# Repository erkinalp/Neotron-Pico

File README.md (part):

# Neotron Pico BTX

> A Neotron system powered by the Raspberry Pi Pico, in a micro-BTX form-factor.

NOTE: This is a work in progress. Proper micro-BTX layout will be uploaded in some time

The Neotron Pico BTX is based around the idea of the [Neotron-32](https://github.com/neotron-compute/Neotron-32-Hardware), but using a low-cost Raspberry Pi Pico instead of a Texas Instuments Tiva-C Launchpad. It also stretches out to full micro-BTX size, and adds more expansion slots so that you can easily design and add your own peripherals.

## Design

The Raspberry Pi Pico is the core of the Neotron Pico. It uses PIO statemachines to generate 12-bit Super VGA video, and digital 16 bit 48 kHz stereo audio. It also has both I²C and SPI buses. SPI chipselects and IRQs are handled by an SPI-to-GPIO expander. This provides eight chip-selects and eight IRQs, to support up to eight expansion slots or peripherals. The eight chip-selects can be globally disabled, allowing the Pico to talk to either the I/O exander, or the selected expansion slot. The board has an SD Card fitted in the 'Slot 1' position, and the Board Management Controller in the 'Slot 0' position, leaving 'Slot 2' through to 'Slot 7' available for expansion. Each expansion slot has both I²C and SPI, along with unique chip-select and IRQ signals.

## Software

The Neotron Pico BTX is designed to run the Neotron OS - a CP/M or MS-DOS alike OS written in Rust. But, being open-hardware, you can program your Neotron Pico to do pretty much anything.

## Specs

* Dual Cortex-M0+
  * One dedicated for video/audio
  * One available for OS/Application use
* 264 KiB SRAM
* 2 MiB Boot ROM
* Micro-ATX form-factor
* SD Card slot for storage
* 12V DC input
* SPI and I²C based expansion bus
  * Four externally accessible expansion slots
  * Debug headers with signals for two more slots
* Dual PS/2 ports for Keyboard + Mouse
* 16-bit 48 kHz stereo audio headphone out, line out, line in, and microphone in
* 12-bit (4096 colour) VGA video output
  * Capable of 40x25, 80x25 and 80x50 text modes
  * Capable of 640x480 @ 60 Hz 16-colour, 320x240 @ 60 Hz / 300x200 @ 70 Hz 256-colour graphics modes
* Designed to run the Neotron OS
* Open Source Hardware
* Perfectly suitable for passive cooling
* Low power
* Designed for hand assembly

## Components in detail

### Processor

The main processor module is the Raspberry Pi Pico, which features:

* A Raspberry Pi Silicon RP2040 SoC
  * Dual-core Cortex-M0+ @ 133 MHz
  * 264 KiB internal SRAM
  * No internal Flash
  * USB 1.1
  * SPI, UART, I²C and _Programmable I/O_ peripherals
* 26 GPIO pins
* 2 MiB QSPI Flash
* On-board LED
* On-board 5V to 3.3V regulator
* USB 2.0 Full-speed OTG micro-AB port
* 4.00 USD / 3.60 GBP retail price

The limited I/O on the Pico (we are using half the available pins just for the video output) is supplemented using a Microchip MCP23S17 SPI to GPIO expander, and an octal buffer. See the [I/O Expanders](#io-expanders) section for more details.

| Pin  | Name | Signal        | Function                                           |
| :--- | :--- | :------------ | :------------------------------------------------- |
| 01   | GP0  | VGA_HSYNC     | VGA Horizontal Sync (31.5 kHz)                     |
| 02   | GP1  | VGA_VSYNC     | VGA Vertical Sync (60 Hz/70 Hz)                    |
| 04   | GP2  | VGA_RED0      | Digital VGA signal, Red channel LSB                |
| 05   | GP3  | VGA_RED1      | Digital VGA signal, Red channel                    |
| 06   | GP4  | VGA_RED2      | Digital VGA signal, Red channel                    |
| 07   | GP5  | VGA_RED3      | Digital VGA signal, Red channel MSB                |
| 09   | GP6  | VGA_GREEN0    | Digital VGA signal, Green channel LSB              |
| 10   | GP7  | VGA_GREEN1    | Digital VGA signal, Green channel                  |
| 11   | GP8  | VGA_GREEN2    | Digital VGA signal, Green channel                  |
| 12   | GP9  | VGA_GREEN3    | Digital VGA signal, Green channel MSB              |
| 14   | GP10 | VGA_BLUE0     | Digital VGA signal, Blue channel LSB               |
| 15   | GP11 | VGA_BLUE1     | Digital VGA signal, Blue channel                   |
| 16   | GP12 | VGA_BLUE2     | Digital VGA signal, Blue channel                   |
| 17   | GP13 | VGA_BLUE3     | Digital VGA signal, Blue channel MSB               |
| 19   | GP14 | I2C_SDA       | I²C Data                                           |
| 20   | GP15 | I2C_SCL       | I²C Clock                                          |
| 21   | GP16 | SPI_CIPO      | SPI Data In                                        |
| 22   | GP17 | nSPI_CS_IO    | Low selects MCP23S17, High selects Peripherals     |
| 24   | GP18 | SPI_CLK       | SPI Clock                                          |
| 25   | GP19 | SPI_COPI      | SPI Data Out                                       |
| 26   | GP20 | nIRQ_IO       | Interrupt Request Input from MCP23S17              |
| 27   | GP21 | nOUTPUT_EN    | Enable buffered CS outputs from MCP23S17           |
| 29   | GP22 | I2S_ADC_DATA  | Digital Audio Input                                |
| 31   | GP26 | I2S_DAC_DATA  | Digital Audio Output                               |
| 32   | GP27 | I2S_BIT_CLOCK | Digital Audio Bit Clock (1.536MHz)                 |
| 34   | GP28 | I2S_LR_CLOCK  | Digital Audio Sync (96kHz)                         |

### Super VGA output

The Raspberry Pi Silicon RP2040 generates 12-bit VGA video at a range of standard resolutions (including 640x480 @ 60 Hz).

* 15-pin D-Sub VGA interface
* 12-bit (4-4-4) RGB R2R DAC
* 3peak TPF133A or Texas Instruments THS7316 RGB video buffer
   * 36 MHz bandwidth - 1024x768@60Hz maximum
   * 6dB gain
   * Drives 75 ohm standard VGA interface
   * SOIC-8 package (1.27mm pitch)
* Texas Instruments TPD7S019 Sync/DDC level shifter and RGB EMC filter
   * SSOP-16 package (0.635mm pitch)

The design could easily be adapted to remove the TPF133A/THS7316 video buffer and the TPD7S019 level shifter/filter, and instead use the [1BitSquared DVI PMOD](https://1bitsquared.com/collections/fpga/products/pmod-digital-video-interface) board if you prefer a DVI output (using an HDMI connector).

### Audio Codec

The audio subsystem offers 16-bit 48 kHz stereo audio in and out through a classic blue/green/pink triple 3.5mm TRS jack. Input and Output volume can be software controlled.

* Texas Instruments TLV320AIC23B
  * I²S + I²C interface
  * Amplified 32mW headphone output and line out
  * Microphone in and line in
  * TSSOP-28 package (0.635mm pitch)
* Triple 3.5mm TRS jack (Kycon STX-4335-5BGP-S1)
  * Headphone Out (green)
  * Line In (blue)
  * Microphone In (pink)
* AC'97 Pin Header for ATX cases with Audio Jacks
  * Headphone Out
  * Microphone In
* Extra line-level output pin header (e.g. for additional RCA audio jacks - operates in addition to 3.5mm headphone jack output)
* Internal line-level input pin header (e.g. for CD-ROM audio - disabled when 3.5mm line-in jack in-use)

### Board Management Controller

Power-on Reset sequencing, soft shutdown, voltage monitoring and PS/2 interfacing is handled by a separate STM32F0 SoC.

* ST Micro STM32F0 (STM32F030K6T6) microcontroller
  * 32-bit Arm Cortex-M0+ Core
  * 3.3V I/O (5V tolerant)
  * 32 KiB Flash
  * 4 KiB SRAM
  * LQFP-32 package (0.8mm pitch)
* Controls two PS/2 ports
* Monitors 5V and 3.3V rails
* Controls system reset, soft-on and soft-off for main CPU
   * Can turn the main 5V regulator on and off
   * Runs from 3.3V stand-by regulator
* SPI interface (with dedicated IRQ line) with main CPU
* Secondary I²C bus, connected to VGA DDC pins

| Pin  | Name | Signal      | Function                                  |
| :--- | :--- | :---------- | :---------------------------------------- |
| 02   | PF0  | BUTTON_nPWR | Power Button Input (active low)           |
| 03   | PF1  | BUTTON_nRST | Reset Button Input (active low)           |
| 06   | PA0  | MON_3V3     | 3.3V rail monitor Input (1.65V nominal)   |
| 07   | PA1  | MON_5V      | 5.0V rail monitor Input (1.65V nominal)   |
| 08   | PA2  | SYS_nRESET  | System Reset Output (active low)          |
| 09   | PA3  | DC_ON       | Enable 5.0V PSU Output (active high)      |
| 10   | PA4  | SPI1_nCS    | SPI Chip Select Input (active low)        |
| 11   | PA5  | SPI1_SCK    | SPI Clock Input                           |
| 12   | PA6  | SPI1_CIPO   | SPI Data Output                           |
| 13   | PA7  | SPI1_COPI   | SPI Data Input                            |
| 14   | PB0  | LED0        | PWM output for first Status LED           |
| 15   | PB1  | LED1        | PWM output for second Status LED          |
| 18   | PA8  | IRQ_nHOST   | Interrupt Output to the Host (active low) |
| 19   | PA9  | I2C1_SCL    | I²C Clock                                 |
| 20   | PA10 | I2C1_SDA    | I²C Data                                  |
| 21   | PA11 | USART1_CTS  | UART Clear-to-Send Output                 |
| 22   | PA12 | USART1_RTS  | UART Ready-to-Receive Input               |
| 23   | PA13 | SWDIO       | SWD Progamming Data Input                 |
| 24   | PA14 | SWCLK       | SWD Programming Clock Input               |
| 25   | PA15 | PS2_CLK0    | Keyboard Clock Input                      |
| 26   | PB3  | PS2_CLK1    | Mouse Clock Input                         |
| 27   | PB4  | PS2_DAT0    | Keyboard Data Input                       |
| 28   | PB5  | PS2_DAT1    | Mouse Data Input                          |
| 29   | PB6  | USART1_TX   | UART Transmit Output                      |
| 30   | PB7  | USART1_RX   | UART Receive Input                        |

Note that in the above table, the UART signals are wired as _Data Terminal Equipment (DTE)_.

This design should also be pin-compatible with the following SoCs (although the software may need recompiling):

* STM32F042K4Tx
* STM32F042K6Tx
* STM32L071KBTx
* STM32L071KZTx
* STM32L072KZTx
* STM32L081KZTx
* STM32L082KZTx

Note that not all STM32 pins are 5V-tolerant, and the PS/2 protocol is a 5V open-collector system, so ensure that whichever part you pick has 5V-tolerant pins (marked `FT` or `FTt` in the datasheet) for the PS/2 signals. All of the parts above _should_ be OK, but they haven't been tested. Let us know if you try one!

### PS/2 Keyboard and Mouse

* Kycon two-port stacked 6-pin DIN sockets (Kycon KMDGX-6S/6S-S4N)
* Controlled via Board Management Controller

### Power Supply

* 12V nominal input
  * 8V to 30V is OK if you don't need the 12V rail
  * Fused with a PTC at 2A
  * Reverse polarity protected
* 3A 5.0V main regulator (DC-DC switch-mode regulator module)
  * Morsun K7805-3AR3
* 200mA 3.3V stand-by regulator (a micropower linear regulator running from 12V input)
* 1A 3.3V regulator (a high-power 1117 type linear regulator running from 5.0V rail)
* Controlled and monitored by the Board Management Controller

### Real Time Clock

The Neotron Pico can retain time/date settings when fully powered off, using a Real Time Clock chip and a CR2032 lithium coin cell. This also retains system settings in a very low-power SRAM built into the Real Time Clock chip.

* MCP7940N or DS1307Z+ Real Time Clock
* CR2032 battery-backup (should be OK for about 10 years)
* 56 bytes of battery-backed SRAM for system settings

### I/O Expander

* MCP23S17 SPI to GPIO expander (DIP)
* 74HC138 3:8 decoder (SOIC-16)
* Five debug LEDs
* Eight Chip-Select outputs (active low)
* Eight IRQ inputs (active high or active low)

Because we used so many pins on the Pico for Audio and Video, we don't have enough pins to use for _Chip Select_ lines. Each device we wish to communicate with on the SPI bus must have a unique chip select line and so have limited lines means we could only have a limited number of SPI devices.

However, in this design, we cheat and use a Microchip MCP23S17 I/O expander. This is an SPI peripheral with 16 GPIO pins that can be controlled by sending it commands over SPI. It also has an IRQ output which be programmed to fire when the input pins match a certain state. The MCP23S18 (with open-drain outputs) will *not* work - it has a different pinout.

The problem would come when the Pico has finished talking to our select SPI device - how does it tell the MCP23S17 to release the current chip select, without the SPI bus traffic also going to the currently selected expansion slot? We resolve this by using a simple 8-bit decoder/buffer with an enable pin. This allows the Pico to disconnect all of the chip select signals at once, regardless of the output of the MCP23S17. Once this is disabled, we know we are talking to only the MCP23S17 and the Pico can command it to select the next chip select of interest to us.

Interrupts are also processed through the MCP23S17. We configure the device to provide an IRQ (edge, active low) whenever any of the eight IRQ inputs are active (programmable for edge or level, active high/rising or low/falling). When the Pico receives an IRQ from the MCP23S17, it must do a read of the pins (using SPI) to find out which device actually raised the interrupt. This model is similar to that used in the IBM PC - where the Intel 8088 must talk to an Intel 8259A programmable interrupt controller over the ISA bus to find out which interrupt was raised - except that in our case, our CPU is very fast and our bus is pretty slow, so our interrupt latency isn't very good. Worse, if there is a big SPI transaction happening (such as transferring a 512 byte block from an SD card) when an interrupt fires, the Pico will have to wait for that to complete before it can talk to the MCP23S17 to handle the IRQ. That or it could just drop the SPI transaction mid-way through and re-try it later (if your expansion device can tolerate such rudeness).

```
+------+                                  +-----+
|      |----------/OUTPUT_EN------------->|     |
|      |                                  |     |
|      |           +----------+           |     |
|      |           |          |           |     |
|      |           |          |--CS_SEL0->|     |----/CS0---------------------------------+
|      |           |          |           |     |                                         |
|      |           |          |--CS_SEL1->|  D  |----/CS1-----------------------------+   |
|      |           |          |           |  E  |                                     |   |
|      |           |          |--CS_SEL2->|  C  |----/CS2-------------------------+   |   |
|      |           |          |           |  O  |                                 |   |   |
|      |           |          |           |  D  |----/CS3---------------------+   |   |   |
|      |           |          |           |  E  |                             |   |   |   |
|      |           |          |           |  R  |----/CS4-----------------+   |   |   |   |
|      |           |          |           |     |                         |   |   |   |   |
|      |           |          |           |     |----/CS5-------------+   |   |   |   |   |
|      |           |          |           |     |                     |   |   |   |   |   |
|      |           |          |           |     |----/CS6---------+   |   |   |   |   |   |
| Pico |           | MCP23S17 |           |     |                 |   |   |   |   |   |   |
|      |           |          |           |     |----/CS7-----+   |   |   |   |   |   |   |
|      |           |          |           +-----+             v   v   v   v   v   v   v   v
|      |           |          |                             +---+---+---+---+---+---+---+---+
|      |--/IOCS--->|          |                             | S | S | S | S | S | S | S | S |
|      |<---IRQ----|          |                             | l | l | l | l | l | l | l | l |
|      |<===SPI===>|          |<============SPI============>| o | o | o | o | o | o | o | o |
|      |           |          |                             | t | t | t | t | t | t | t | t |
|      |           |          |                             |   |   |   |   |   |   |   |   |
|      |           |          |                             | 7 | 6 | 5 | 4 | 3 | 2 | 1 | 0 |
|      |           |          |                             +---+---+---+---+---+---+---+---+
|      |           |          |<---IRQ7-----------------------+   |   |   |   |   |   |   |
|      |           |          |                                   |   |   |   |   |   |   |
|      |           |          |<---IRQ6---------------------------+   |   |   |   |   |   |
|      |           |          |                                       |   |   |   |   |   |
|      |           |          |<---IRQ5-------------------------------+   |   |   |   |   |
|      |           |          |                                           |   |   |   |   |
|      |           |          |<---IRQ4-----------------------------------+   |   |   |   |
|      |           |          |                                               |   |   |   |
|      |           |          |<---IRQ3---------------------------------------+   |   |   |
|      |           |          |                                                   |   |   |
|      |           |          |<---IRQ2-------------------------------------------+   |   |
|      |           |          |                                                       |   |
|      |           |          |<---IRQ1-----------------------------------------------+   |
|      |           |          |                                                           |
|      |           |          |<---IRQ0---------------------------------------------------+
+------+           +----------+
```

## Expansion

The seven expansion sockets allow you to add on I²C or SPI based devices at a later date. Each provides a single chip-select and a single IRQ line - the motherboard design should ensure each socket gets a unique signal for each of these. Each expansion device should also contain a AT24C256 or similar EEPROM device. To allow these EEPROM devices to be scanned, each slot also contains three `EEPROM_ADDRESS` pins, tied to Vcc or GND in a unique combination. These should be connected through to the EEPROM address lines on your AT24C256, thus ensuring that each expansion card has its EEPROM at a unique address - 0x50 on Slot 0 through to a maximum possible 0x57 for Slot 7. Where your board has on-board devices, you should fit an AT24C256 EEPROM for each device so that the on-board devices can be discovered, exactly as if they were on an expansion card.

The expansion slot is a simple 2x10 header. We suggest the use of a TE card-edge connector, but you could equally use two 1x10 pin-headers if desired.

The expansion connector pinout is:

```
               +--------+
     SPI_COPI -| 1    2 |- GND
     SPI_CIPO -| 3    4 |- GND
      SPI_CLK -| 5    6 |- GND
      ~SPI_CS -| 7    8 |- ~IRQ
      I2C_SDA -| 9   10 |- I2C_SCL
 EEPROM_ADDR0 -| 11  12 |- EEPROM_ADDR1
 EEPROM_ADDR2 -| 13  14 |- ~RESET
           5V -| 15  16 |- 5V
          3V3 -| 17  18 |- 3V3
          GND -| 19  20 |- GND
               +--------+
```

Four expansion slots line up with the ATX case expansion brackets, allowing you to use cards with external connectors. Note that these are aligned the "PCI way around" with components facing away from the board's I/O area, rather than the "ISA way around" which would have the components facing the I/O area. A further three of the expansion slots are available for internal use only.

### Slot Assignments

#### Slot 0

The signals for *Slot 0* are connected to the Board Management Controller. Both CS and IRQ are connected.

#### Slot 1

The signals for *Slot 1* are connected to the on-board SD Card Slot. CS 1 is connected to the card's `DAT3` pin, and IRQ 1 is connected to the `Card Detect` pin on the card slot.

#### Slot 2

*Slot 2* is the right-most Expansion Slot.

#### Slot 3

*Slot 3* is the right-most-but-one Expansion Slot.

#### Slot 4

*Slot 4* is the left-most-but-one Expansion Slot.

#### Slot 5

*Slot 5* is the left-most Expansion Slot.

#### Slot 6

*Slot 6* is not fitted. SPI Chip Select 6 and IRQ 6 are only available on the test headers. 

#### Slot 7

*Slot 7* is not fitted. SPI Chip Select 7 and IRQ 7 are only available on the test headers. 

### Main I²C Bus

All I²C device address given below are 7-bit values. Note that with I²C, the first byte in a message is the _control byte_; this is comprised of the device address in the top seven bits, and an extra bit at the bottom to indicate read (1) or write (0).

The memory addresses given are 8-bit values used to access the contents of an I²C device, and are usually supplied as the second byte in a message.

* Device Address 0x1A - TLV320AIC23
  * Memory Address 0x00 - Left line input channel volume control
  * Memory Address 0x01 - Right line input channel volume control
  * Memory Address 0x02 - Left channel headphone volume control
  * Memory Address 0x03 - Right channel headphone volume control
  * Memory Address 0x04 - Analog audio path control
  * Memory Address 0x05 - Digital audio path control
  * Memory Address 0x06 - Power down control
  * Memory Address 0x07 - Digital audio interface format
  * Memory Address 0x08 - Sample rate control
  * Memory Address 0x09 - Digital interface activation
  * Memory Address 0x0F - Reset register
* Device Address 0x52 - Slot 2 ID EEPROM
  * Memory Addresses 0x00..0xFF - Expansion Card Specification in NEID (Neotron Expansion ID) format
* Device Address 0x53 - Slot 3 ID EEPROM
  * Memory Addresses as per Slot 1
* Device Address 0x54 - Slot 4 ID EEPROM
  * Memory Addresses as per Slot 1
* Device Address 0x55 - Slot 5 ID EEPROM
  * Memory Addresses as per Slot 1
* Device Address 0x68 - Real-time Clock (DS1307+ variant)
  * Memory Addresses 0x00..0x07 - Clock Configuration
  * Memory Addresses 0x08..0x3F - Battery-backed SRAM
* Device Address 0x6F - Real-time Clock (MCP7940N variant)
  * Memory Addresses 0x00..0x1F - Clock Configuration
  * Memory Addresses 0x20..0x5F - Battery-backed SRAM

### Secondary I²C Bus

There is a second I²C bus, driven by the Board Management Controller. This is connected to the Display Data Connection (DDC) pins on the VGA interface, allowing the reading of the VGA monitor's [EDID block](https://en.wikipedia.org/wiki/Extended_Display_Identification_Data). This is typically at device address `0x50`

## Expansion Ideas

Why not design and build your own expansion card? You could try designing:

* A dual Atari/SEGA 9-pin Joypad Interface
* A Mikro Electronika Click adaptor, allow many of the range of [Click boards](https://www.mikroe.com/click) to be fitted
* A Wi-Fi/Bluetooth card, using an Espressif ESP32-C3
* A second processor card - perhaps with a RISC-V microcontroller, or classic Zilog Z80
* An OPL2 or OPL3 based FM synthesiser card
* An ISA adaptor card (taking an ISA card at right-angles, i.e. parallel to the base board) - a simple microcontroller should be able to bit-bang the ISA bus at 8 MHz and offer an SPI peripheral interface to the Neotron Expansion Slot
* An IDE interface card, allowing 40-pin IDE Hard Disk Drives and CD-ROM drives to be used - this will be quite similar to an ISA bus adaptor
* A floppy drive controller card - either using an eSPI Super I/O chip, or connecting a legacy ISA bus floppy controller as per the ISA adaptor
* A video card for a second monitor output, perhaps based on the CPLD used in the [VGAtonic](https://hackaday.io/project/6309-vga-graphics-over-spi-and-serial-vgatonic)

## Automated Builds

This project treats a PCB like embedded firmware:

* The *source files* are the KiCAD 6 files (in `./Kicad`)
* The *compiler* is KiCAD 6, plus various automation plug-ins (like KiBom)
* The *build system* is [KiBot](https://github.com/INTI-CMNB/KiBot)
* The *build outputs* are PDF versions of the schematic and the PCB, plus various zipped Gerber and Drill files.

We do not check *build outputs* into this repository - *ever*. Instead, we run a Github Action which uses KiBot to generate our outputs. On a regular Pull Request, the *build outputs* are stored as *artefacts* against the particular Github Action run. When a new version is tagged, the *build outputs* are stored as files against a [Github Release](https://github.com/Neotron-Compute/Neotron-Pico/releases).

You can build locally using the KiBot docker container:

```console
~/Neotron-Pico $ docker run --rm -ti -v $(pwd):/work setsoft/kicad_auto:dev_k6
root@12345678:/# cd /work/Kicad
root@12345678:/work/Kicad# kibot -c docs.kibot.yml -e neotron-pico.kicad_sch -b neotron-pico.kicad_pcb -d docs
```

This will build everything and put it in the `./Kicad/docs` directory.

## Changelog

See [CHANGELOG.md](./CHANGELOG.md) for a list of detailed changes.

## Licence

These documents, schematics and PCB designs are Copyright (c) The Neotron Developers, 2022.

This work is licensed under a [Creative Commons Attribution-ShareAlike 4.0 International License](http://creativecommons.org/licenses/by-sa/4.0/).

That means you are free to:

* share - copy and redistribute the material in any medium or format
* adapt — remix, transform, and build upon the material for any purpose, even commercially

Please note that the models provided in the [Kicad/Models](./Kicad/Models) directory are from various manufacturers. Terms and conditions for the use of the models are as specified by the original manufacturer/author.

__NOTE__: Releases are provided free-of-charge, and without any kind of warranty - explicit or implied. It is imperative you validate the design for yourself before placing an order or using/adapting/copying any of the designs herein. The Neotron Developers cannot be held responsible if you build or remix our designs and it doesn't turn out how you expected. This is a work-in-progress and you will most likely need to fix something, somewhere.

## Contribution Agreement

Unless you explicitly state otherwise, any contribution intentionally submitted for inclusion in the work by you, as defined in the Apache-2.0 license, shall be licensed as above, without any additional terms or conditions.

## Articles and Reviews

* [Tom's Hardware](https://www.tomshardware.com/uk/news/raspberry-pi-pico-neotron-motherboard)
* [Tom's Hardware #2](https://www.tomshardware.com/uk/news/raspberry-pi-pico-motherboard-update-neotron-pico)
* [Hackaday](https://hackaday.com/2021/06/22/pi-pico-powered-atx-motherboard/)
* [Hackster.io](https://www.hackster.io/news/jonathan-pallant-s-neotron-pico-turns-the-raspberry-pi-pico-into-a-full-size-atx-pc-motherboard-fff86e2a1a96)
* [Hacker News](https://news.ycombinator.com/item?id=27627631)
* [Adafruit Blog](https://blog.adafruit.com/2021/06/23/a-raspberry-pi-pico-based-computer-motherboard/)

## Datasheets and References

* Raspberry Pi Pico
  * Datasheet: <https://datasheets.raspberrypi.org/pico/pico-datasheet.pdf>
* Raspberry Pi Silicon RP2040
  * Datasheet: <https://datasheets.raspberrypi.org/rp2040/rp2040-datasheet.pdf>
  * Hardware Design Guide: <https://datasheets.raspberrypi.org/rp2040/hardware-design-with-rp2040.pdf>
* ST Microelectronics STM32F031K6T6
  * Datasheet: <https://www.st.com/resource/en/datasheet/stm32f031k6.pdf>
* Morsun K7805-3AR3
  * Datasheet: <https://www.mornsunpower.de/html/pdf/K7805-3AR3.html>
* Texas Instruments TLV320AIC23BPW
  * Datasheet: <https://www.ti.com/lit/ds/symlink/tlv320aic23b.pdf>
  * Note TLV320AIC23B**I**PW is Industrial Temperature Range (and is fine to use), and TLV320AIC23BPW**R** is on a Reel (also fine)
* Texas Instruments THS7316
  * Datasheet: <https://www.ti.com/lit/ds/symlink/ths7316.pdf>
* Texas Instruments TPD7S019
  * Datasheet: <https://www.ti.com/lit/ds/symlink/tpd7s019.pdf>
* Microchip 24LC256 EEPROM
  * Info Page: <https://www.microchip.com/wwwproducts/en/24LC256>
* Microchip MCP7940N Real-Time Clock
  * Info Page: <https://www.microchip.com/wwwproducts/en/MCP7940N>

## How hard is this to solder?

Typically, I get the boards from JLCPCB with most of the surface-mount components already fitted. This includes all the LEDS, small inductors, resistors and small capacitors (all 0805 size), the transistors (all SOT-23), and whichever of the larger ICs they happen to have in stock. All that's left is the larger ICs, and the through-hole connectors.

In the release area, you will see a JLCPCB specific bill-of-materials (BoM), which includes only the parts with a `Cxxxx` format LCSC/JLCPCB part number. You upload this, along with the *CPL* position file for those parts, when placing your order.

If you want to order bare boards, it is designed to be hand-solderable. That's why there are no SMD parts smaller than 0805.

| Part           | Footprint | Size (mm) | Pitch (mm) |
|:---------------|:---------:|:---------:|:----------:|
| MCP23S17       |  DIP-28   |  36x7.6   |    2.54    |
| Jellybeans     |   0805    |  2.0x1.2  |    N/A     |
| Transistors    |  SOT-23   |  3.1x1.4  |    1.80    |
| 74HC138        |  SOIC-16  |  3.9x9.9  |    1.27    |
| THS7316        |  SOIC-8   |  3.9x4.9  |    1.27    |
| DS1307Z        |  SOIC-8   |  3.9x4.9  |    1.27    |
| STM32F031K6T6  |  LQFP-32  |  7.0x7.0  |    0.80    |
| TLV320AIC23BPW | TSSOP-28  |  4.4x9.7  |    0.65    |
| TPD7S019       |  SSOP-16  |  3.9x4.9  |   0.635    |

## But can I buy the parts yet?

Feel free to click these (unaffiliated) links and see for yourself!

| Component               | Manufacturer      | Part Number     | Octopart                                                                     | LCSC                                                                                                                | JLCPCB                                                                                | Digikey                                                                                                 | Mouser                                                                                                          | RS                                                                            | Farnell                                                                                                        |
| :---------------------- | :---------------- | :-------------- | :--------------------------------------------------------------------------- | :------------------------------------------------------------------------------------------------------------------ | :------------------------------------------------------------------------------------ | :------------------------------------------------------------------------------------------------------ | :-------------------------------------------------------------------------------------------------------------- | :---------------------------------------------------------------------------- | :------------------------------------------------------------------------------------------------------------- |
| Main CPU                | Raspberry Pi      | Pico (SC0915)   | [Link](https://octopart.com/raspberry+pi+pico-raspberry+pi-116179381?r=sp)   | N/A                                                                                                                 | N/A                                                                                   |                                                                                                         |                                                                                                                 | N/A                                                                           | [Link](https://uk.rs-online.com/web/p/raspberry-pi/2122162)                                                    |
| BMC                     | ST Micro          | STM32F030K6T6   | [Link](https://octopart.com/stm32f030k6t6-stmicroelectronics-30038872?r=sp)  | [C46830](https://www.lcsc.com/product-detail/ST-Microelectronics_STMicroelectronics-STM32F030K6T6_C46830.html)      | [C46830](https://jlcpcb.com/parts/componentSearch?isSearch=true&searchTxt=C46830)     | [Tray](https://www.digikey.co.uk/en/products/detail/stmicroelectronics/STM32F030K6T6/4494296)           | [Link](https://www.mouser.co.uk/ProductDetail/STMicroelectronics/STM32F030K6T6?qs=eyrSuY1LhL2nYlb0JDdrAA%3D%3D) | [Link](https://uk.rs-online.com/web/p/microcontrollers/8294644)               | [Link](https://uk.farnell.com/stmicroelectronics/stm32f030k6t6/mcu-32bit-cortex-m0-48mhz-lqfp/dp/2432085)      |
| BMC (alt)               | ST Micro          | STM32F031K6T6   | [Link](https://octopart.com/stm32f031k6t6-stmicroelectronics-35036651?r=sp)  | [C526904](https://www.lcsc.com/product-detail/ST-Microelectronics_STMicroelectronics-STM32F031K6T6_C526904.html)    | [C526904](https://jlcpcb.com/parts/componentSearch?isSearch=true&searchTxt=C526904)   | [Tray](https://www.digikey.co.uk/en/products/detail/stmicroelectronics/STM32F031K6T6/5051261)           | [Link](https://www.mouser.co.uk/ProductDetail/STMicroelectronics/STM32F031K6T6?qs=s5SkPsIz109XuZAtCLiKdA%3D%3D) | [Link](https://uk.rs-online.com/web/p/microcontrollers/1920937)               | [Link](https://uk.farnell.com/stmicroelectronics/stm32f031k6t6/mcu-32bit-48mhz-lqfp-32/dp/3129831)             |
| Video Amplifier         | Texas Instruments | THS7316         | [Link](https://octopart.com/ths7316dr-texas+instruments-7112464?r=sp)        | [C544774](https://www.lcsc.com/product-detail/Operational-Amplifier_Texas-Instruments-THS7316DR_C544774.html)       | [C544774](https://jlcpcb.com/parts/componentSearch?isSearch=true&searchTxt=C544774)   | [Tape](https://www.digikey.co.uk/en/products/detail/texas-instruments/THS7316DR/1905373)                | N/A                                                                                                             | N/A                                                                           | N/A                                                                                                            |
| Video Amplifier (alt 1) | 3Peak             | TPF133A         | [Link](https://octopart.com/tpf133a-sr-3peak-99349217?r=sp)                  | [C155446](https://www.lcsc.com/product-detail/Video-Amplifiers_3PEAK-TPF133A-SR_C155446.html)                       | [C155446](https://jlcpcb.com/parts/componentSearch?isSearch=true&searchTxt=C155446)   | N/A                                                                                                     | N/A                                                                                                             | N/A                                                                           | N/A                                                                                                            |
| Video Amplifier (alt 2) | DIOO              | DIO2663         | [Link](https://octopart.com/dio2663cs8-dioo-120986996?r=sp)                  | [C444605](https://lcsc.com/product-detail/Video-Amplifiers_DIOO-DIO2663CS8_C444605.html)                            | [C444605](https://jlcpcb.com/parts/componentSearch?isSearch=true&searchTxt=C444605)   | N/A                                                                                                     | N/A                                                                                                             | N/A                                                                           | N/A                                                                                                            |
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
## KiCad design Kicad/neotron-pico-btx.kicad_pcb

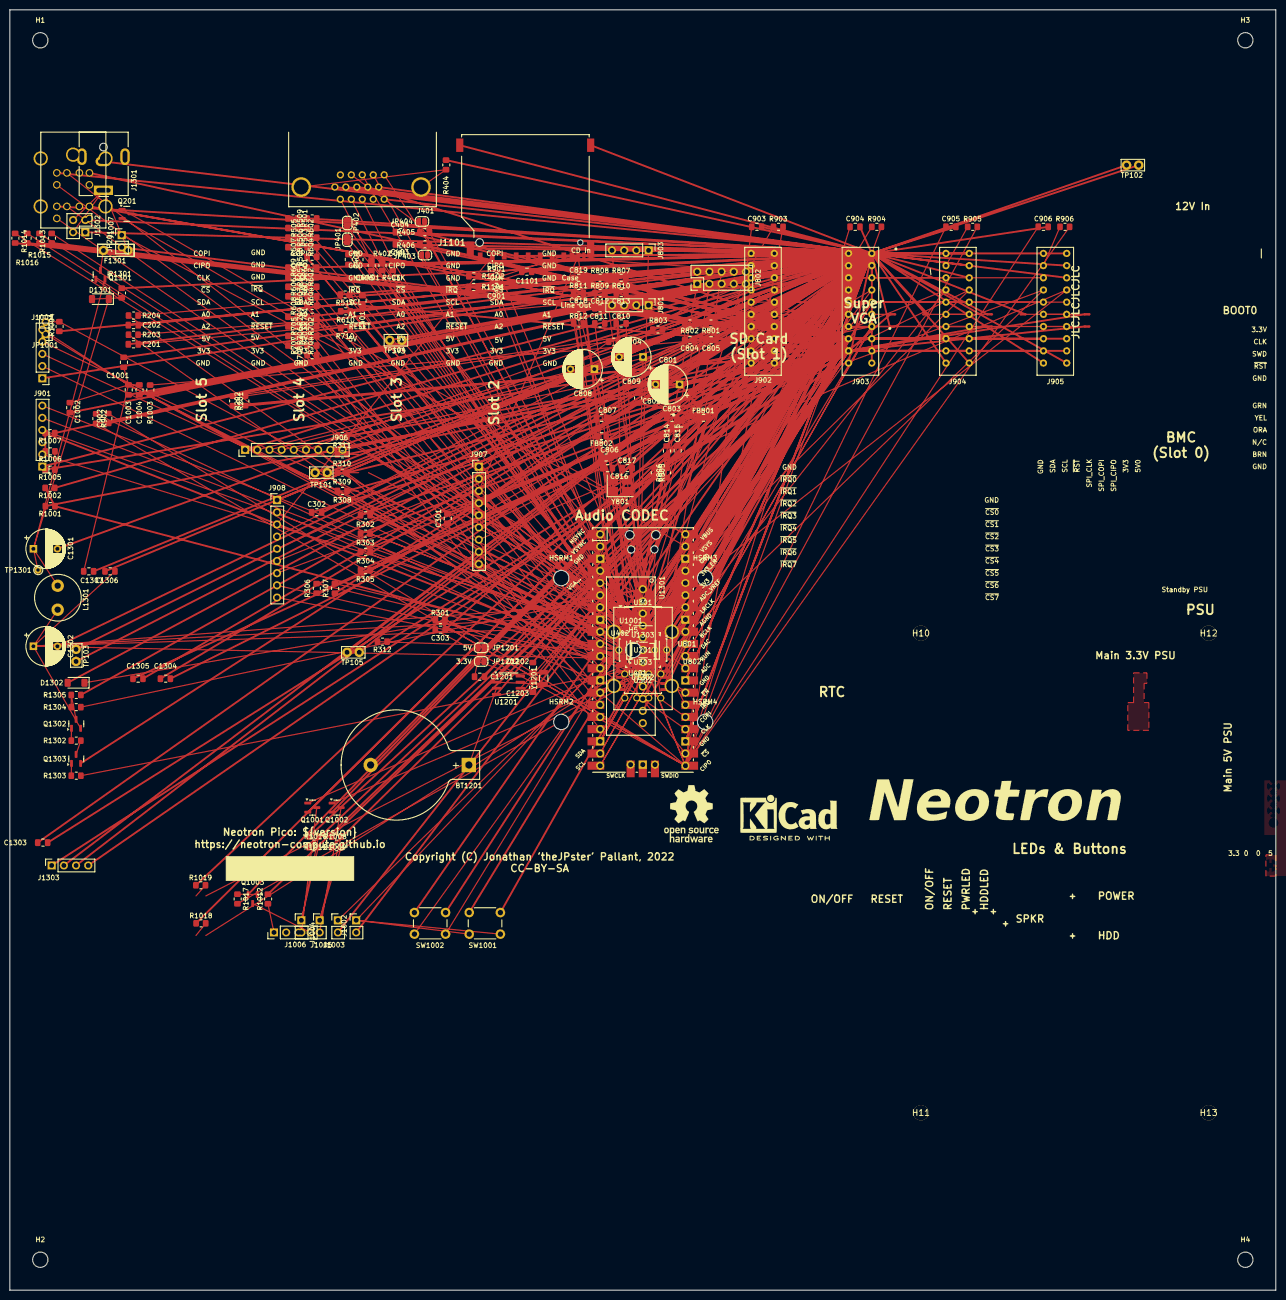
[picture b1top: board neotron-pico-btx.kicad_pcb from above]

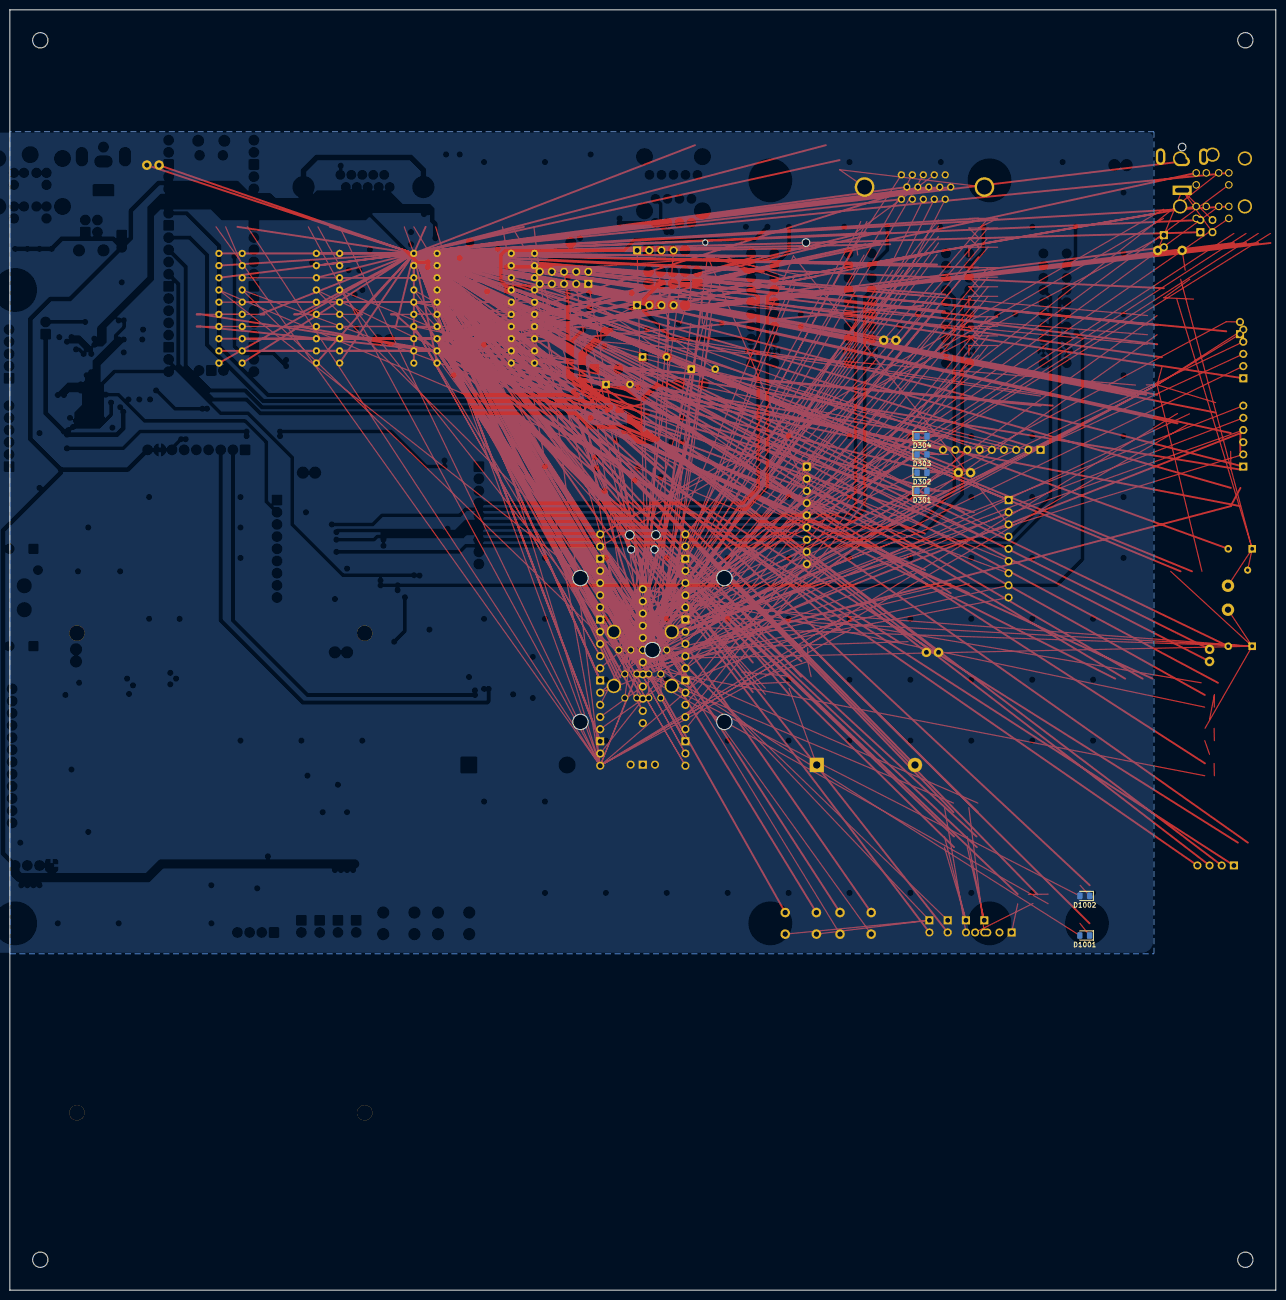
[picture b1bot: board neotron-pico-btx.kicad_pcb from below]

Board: 4 copper layers, 264.0 x 267.0 mm, 248 parts (6 on the bottom side), 190 nets.

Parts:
BT1201: CR2032; BatteryHolder_Keystone_103_1x20mm
C201, C202, C303, C901, C902, C903, C904, C905, C906, C1202, C1203: DNF; C_0805_2012Metric_Pad1.18x1.45mm_HandSolder
C301, C302, C401, C403, C404, C405, C802, C803, C806, C807, C815, C1001, C1002, C1004, C1101, C1201, C1306, C1307: 10u; C_0805_2012Metric_Pad1.18x1.45mm_HandSolder
C402: 220n; C_0805_2012Metric_Pad1.18x1.45mm_HandSolder
C801, C808, C809, C1301, C1302: 100u; CP_Radial_D8.0mm_P5.00mm
C804, C805, C810, C811, C818: 1u; C_0805_2012Metric_Pad1.18x1.45mm_HandSolder
C812, C813, C819: 47p; C_0805_2012Metric_Pad1.18x1.45mm_HandSolder
C814: 100n; C_0805_2012Metric_Pad1.18x1.45mm_HandSolder
C816, C817: 22p; C_0805_2012Metric_Pad1.18x1.45mm_HandSolder
C1003: 10n; C_0805_2012Metric_Pad1.18x1.45mm_HandSolder
C1303, C1304, C1305: 22u; C_0805_2012Metric_Pad1.18x1.45mm_HandSolder
D301, D302, D303, D304, D1001, D1002: LED; LED_0805_2012Metric_Pad1.15x1.40mm_HandSolder
D1301, D1302: ZMM5V6; D_MiniMELF
F1301: 32V 2A PTC; Bel Fuse 0ZRS0200FF
FB801, FB802: 330R@100MHz; L_0805_2012Metric_Pad1.15x1.40mm_HandSolder
H1, H2, H3, H4, H5: MountingHole_3.2mm_M3
H10, H11, H12, H13: MOUNT_HOLE_SRM
HSRM1, HSRM2, HSRM3, HSRM4: MountingHole_3.2mm_M3
J401: DE15HD; Amphenol_ICD15S13E4GV00LF
J801, J803, J1006: Conn_01x04; PinHeader_1x04_P2.54mm_Vertical
J802: Conn_02x05; PinHeader_2x05_P2.54mm_Vertical
J901: Conn_01x06; PinHeader_1x06_P2.54mm_Vertical
J902, J903, J904, J905: Neotron-Expansion-Slot
J906, J907, J908: Conn_01x09; PinHeader_1x09_P2.54mm_Vertical
J1001: Conn_01x05; PinHeader_1x05_P2.54mm_Vertical
J1002, J1003, J1004, J1005: Conn_01x02; PinHeader_1x02_P2.54mm_Vertical
J1007: Double-mini-DIN-6; Double_mini-DIN_6
J1101: SD_Card; Amphenol_GSD090012SEU
J1301: Jack 2.1mm 6.3mm; BarrelJack_CUI_PJ-063AH_Horizontal
J1302: Conn_02x02S; PinSocket_2x02_P2.54mm_Vertical
J1303: Conn_01x04S; PinSocket_1x04_P2.54mm_Vertical
JP201, JP1001: Jumper; PinHeader_1x02_P2.54mm_Vertical
JP401, JP402, JP403, JP404, JP1201, JP1202: Bridge; SolderJumper-2_P1.3mm_Open_RoundedPad1.0x1.5mm
L1301: 22uH; L_Radial_D9.5mm_P5.00mm_Fastron_07HVP
LOGO101: Neotron Logo; logo
LOGO102: Kicad Logo; KiCad-Logo2_8mm_SilkScreen
LOGO103: OSHW Logo; OSHW-Logo_11.4x12mm_SilkScreen
NT901, NT902, NT903, NT904, NT905, NT906, NT907, NT908, NT909, NT910, NT911, NT912: NetTie_2; NetTie-2_SMD_Pad0.5mm
Q201: DMG2305UX; SOT-23
Q1001, Q1002: 2N7002; SOT-23
Q1003, Q1303: SS8050; SOT-23
Q1301: AO3401A; SOT-23
Q1302: SS8550; SOT-23
R201, R202, R405, R406, R501, R502, R503, R504, R509, R601, R602, R603, R604, R609, R701, R702, R703, R704, R709, R811: 2k; R_0805_2012Metric_Pad1.20x1.40mm_HandSolder
R203, R204, R301, R805, R806, R812, R901, R902, R903, R904, R905, R906: 0R; R_0805_2012Metric_Pad1.20x1.40mm_HandSolder
R302, R303, R304, R305, R306, R307, R312, R1001, R1002, R1003, R1004, R1005, R1006, R1007, R1101, R1102, R1301, R1302, R1303, R1305: 10k; R_0805_2012Metric_Pad1.20x1.40mm_HandSolder
R308, R309, R310, R311, R505, R506, R507, R508, R605, R606, R607, R608, R705, R706, R707, R708, R1013, R1014, R1015, R1016, R1017, R1018, R1019, R1304: 1k; R_0805_2012Metric_Pad1.20x1.40mm_HandSolder
R401, R402, R403: 75; R_0805_2012Metric_Pad1.20x1.40mm_HandSolder
R404: DNF; R_0805_2012Metric_Pad1.20x1.40mm_HandSolder
R510, R610, R710: 560; R_0805_2012Metric_Pad1.20x1.40mm_HandSolder
R801, R802, R803, R804: 100k; R_0805_2012Metric_Pad1.20x1.40mm_HandSolder
R807, R808, R809, R810: 4k7; R_0805_2012Metric_Pad1.20x1.40mm_HandSolder
R1008, R1009, R1010, R1011: 300; R_0805_2012Metric_Pad1.20x1.40mm_HandSolder
R1012: 33R; R_0805_2012Metric_Pad1.20x1.40mm_HandSolder
SW1001, SW1002: SW_Push; SW_PUSH_6mm
TP101, TP102, TP103, TP104, TP105: TestPoint; TestPoint_Bridge_Pitch2.54mm_Drill1.0mm
TP1301: PTH; TestPoint_THTPad_D1.5mm_Drill0.7mm
U201: Pico; RPi_Pico_SMD_TH
U301: MCP23S17_SO; SOIC-28W_7.5x17.9mm_P1.27mm
U302: 74HC138; SOIC-16_3.9x9.9mm_P1.27mm
U303: 74AHC1G04; SOT-23-5_HandSoldering
U401: THS7316; SOIC-8_3.9x4.9mm_P1.27mm
U402: TPD7S019; SSOP-16_3.9x4.9mm_P0.635mm
U801: TLV320AIC23BPW; TSSOP-28_4.4x9.7mm_P0.65mm
U802: STX-4335-5BGP-S1
U1001: STM32F030K6T6; LQFP-32_7x7mm_P0.8mm
U1201: DS1307Z+; SOIC-8_3.9x4.9mm_P1.27mm
U1301: DC-DC Module; K78xx-3AR3
U1302: AMS1117-3.3; SOT-223-3_TabPin2
U1303: HT75xx-1-SOT89; SOT-89-3
Y801: 12M 20pF; Crystal_SMD_3225-4Pin_3.2x2.5mm_HandSoldering
Y1201: 32,768 Hz; Crystal_SMD_3215-2Pin_3.2x1.5mm

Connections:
+3.3VP: C1001.2, C1002.2, C1003.1, C1004.2, C1307.2, J1001.5, JP1001.1 (A), U1001.1 (VDD), U1001.5 (VDDA), U1001.17 (VDD), U1303.3 (VOUT)
+3V3: C301.1, C302.1, C401.1, C405.2, C1101.2, C1305.1, FB801.2, FB802.2, J902.17 (3V3), J902.18 (3V3), J903.17 (3V3), J903.18 (3V3), J904.17 (3V3), J904.18 (3V3), J905.17 (3V3), J905.18 (3V3), J906.8, J1101.4 (VDD), J1303.1, JP1202.2 (B), NT902.2, NT904.2, NT905.2, NT906.2, NT911.2, NT912.2, R201.2, R202.2, R302.1, R303.1, R304.1, R305.1, R306.1, R308.1, R309.1, R310.1, R311.1, R312.1, R1001.1, R1101.2, R1102.1, U301.9 (VDD), U302.16 (VCC), U303.5 (VCC), U401.4 (Vcc), U402.7 (VCC_DDC), U1302.2 (VO)
+5V: C403.2, C404.2, C1303.1, C1304.1, J401.9, J802.7, J902.15 (5V), J902.16 (5V), J903.15 (5V), J903.16 (5V), J904.15 (5V), J904.16 (5V), J905.15 (5V), J905.16 (5V), J906.9, J1007.4, J1007.10, J1303.4, JP201.2 (B), JP1201.2 (B), Q201.3 (D), R405.1, R406.1, R1005.1, R1008.1, R1009.1, R1010.1, R1011.1, R1012.2, R1013.1, R1014.1, R1015.1, R1016.1, U402.1 (VCC_SYNC), U402.2 (VCC_VIDEO), U1301.4 (Vo), U1302.3 (VI)
/Audio/3V3_ANALOG: C801.1, C802.1, C803.1, FB801.1, U801.8 (HPVDD), U801.14 (AVDD)
/Audio/3V3_DIGITAL: C806.1, C807.1, FB802.1, U801.1 (BVDD), U801.27 (DVDD)
/Audio/AUDIO_ADC_DATA: U201.29 (GPIO22), U801.6 (DOUT)
/Audio/AUDIO_ADC_LR: U201.34 (GPIO28_ADC2), U801.5 (LRCIN), U801.7 (LRCOUT)
/Audio/AUDIO_BIT_CLK: U201.32 (GPIO27_ADC1), U801.3 (BCLK)
/Audio/AUDIO_DAC_DAT: U201.31 (GPIO26_ADC0), U801.4 (DIN)
/Audio/CDInL: J803.1, U802.34 (BlueTipOut)
/Audio/CDInR: J803.4, U802.33 (BlueRingOut)
/Audio/FrontHPL: C808.2, J802.9, R804.2
/Audio/FrontHPR: C809.2, J802.5, R803.1
/Audio/FrontMicAudio: J802.1, U802.4 (PinkTipOut)
/Audio/FrontMicBias: J802.3, U802.3 (PinkRingOut)
/Audio/LHpOut: C808.1, U801.9 (LHPOUT)
/Audio/LLineIn: C810.2, U801.20 (LLINEIN)
/Audio/LOut: C804.1, U801.12 (LOUT)
/Audio/LineOutL: C804.2, J801.1, R802.2
/Audio/LineOutR: C805.1, J801.4, R801.1
/Audio/MicBias: R811.2, U801.17 (MICBIAS)
/Audio/MicIn: R812.1, U801.18 (MICIN)
/Audio/RHpOut: C809.1, U801.10 (RHPOUT)
/Audio/RLineIn: C811.2, U801.19 (RLINEIN)
/Audio/ROut: C805.2, U801.13 (ROUT)
/Audio/RearHPL: J802.10, U802.25 (LimeTip)
/Audio/RearHPR: J802.6, U802.22 (LimeRing)
/Audio/RearInL: R807.1, U802.35 (BlueTip)
/Audio/RearInR: R808.1, U802.32 (BlueRing)
/Audio/RearMicAudio: C818.1, C819.2, U802.5 (PinkTip)
/Audio/RearMicBias: R811.1, U802.2 (PinkRing)
/Audio/VMID: C814.1, C815.1, U801.16 (VMID)
/BLUE0: R701.1, U201.14 (GPIO10)
/BLUE1: R702.1, U201.15 (GPIO11)
/BLUE2: R703.1, U201.16 (GPIO12)
/BLUE3: R704.1, U201.17 (GPIO13)
/GREEN0: R601.1, U201.9 (GPIO6)
/GREEN1: R602.1, U201.10 (GPIO7)
/GREEN2: R603.1, U201.11 (GPIO8)
/GREEN3: R604.1, U201.12 (GPIO9)
/IO Expander/CS_SEL0: R302.2, U301.21 (GPA0), U302.1 (A0)
/IO Expander/CS_SEL1: R303.2, U301.22 (GPA1), U302.2 (A1)
/IO Expander/CS_SEL2: R304.2, U301.23 (GPA2), U302.3 (A2)
/IO Expander/E2: R307.1, U302.5 (E2)
/IO Expander/E3: R306.2, U302.6 (E3)
/IO Expander/HDD_LED: D1001.2 (A), Q1001.1 (G), U303.4
/IO Expander/~CS0: J908.2, U302.15 (O0), U1001.10 (PA4)
/IO Expander/~CS1: J908.3, J1101.1 (CD/DAT3), U302.14 (O1)
/IO Expander/~CS2: J902.7 (~SPI_CS), J908.4, U302.13 (O2)
/IO Expander/~CS3: J903.7 (~SPI_CS), J908.5, U302.12 (O3)
/IO Expander/~CS4: J904.7 (~SPI_CS), J908.6, U302.11 (O4)
/IO Expander/~CS5: J905.7 (~SPI_CS), J908.7, U302.10 (O5)
/IO Expander/~CS6: J908.8, U302.9 (O6)
/IO Expander/~CS7: J908.9, U302.7 (O7)
/IO Expander/~IRQ0: J907.2, U301.1 (GPB0), U1001.18 (PA8)
/IO Expander/~IRQ1: J907.3, J1101.10 (CARD_DETECT), R1101.1, U301.2 (GPB1)
/IO Expander/~IRQ2: J902.8 (~IRQ), J907.4, U301.3 (GPB2)
/IO Expander/~IRQ3: J903.8 (~IRQ), J907.5, U301.4 (GPB3)
/IO Expander/~IRQ4: J904.8 (~IRQ), J907.6, U301.5 (GPB4)
/IO Expander/~IRQ5: J905.8 (~IRQ), J907.7, U301.6 (GPB5)
/IO Expander/~IRQ6: J907.8, U301.7 (GPB6)
/IO Expander/~IRQ7: J907.9, U301.8 (GPB7)
/IO Expander/~IRQ_IO: U201.26 (GPIO20), U301.19 (INTB)
/IO Expander/~LED0: R312.2, U301.24 (GPA3), U303.2
/IO Expander/~LED1: D301.1 (K), U301.25 (GPA4)
/IO Expander/~LED2: D302.1 (K), U301.26 (GPA5)
/IO Expander/~LED3: D303.1 (K), U301.27 (GPA6)
/IO Expander/~LED4: D304.1 (K), U301.28 (GPA7)
/IO Expander/~OUTPUT_EN: R305.2, U201.27 (GPIO21), U302.4 (E1)
/IO Expander/~SPI_CS: U201.22 (GPIO17), U301.11 (~CS)
/Power Supply/DC_ON: R1303.2, U1001.9 (PA3)
/Power Supply/PSU_CTRL: D1302.1 (K), R1304.1, U1301.1 (Ctrl)
/RED0: R501.1, U201.4 (GPIO2)
/RED1: R502.1, U201.5 (GPIO3)
/RED2: R503.1, U201.6 (GPIO4)
/RED3: R504.1, U201.7 (GPIO5)
/Real Time Clock/BATT_PWR: BT1201.1 (+), U1201.3 (VBAT)
/Slots and Peripherals/BMC/BUZZER: R1017.1, U1001.15 (PB1)
/Slots and Peripherals/BMC/LED0: D1002.2 (A), Q1002.1 (G), U1001.14 (PB0)
/Slots and Peripherals/BMC/MON_3V3: R1001.2, R1002.1, U1001.6 (PA0)
/Slots and Peripherals/BMC/MON_5V: R1006.2, R1007.1, U1001.7 (PA1)
/Slots and Peripherals/BMC/PS2_CLK0: J1007.5, R1013.2, U1001.25 (PA15)
/Slots and Peripherals/BMC/PS2_CLK1: J1007.11, R1015.2, U1001.26 (PB3)
/Slots and Peripherals/BMC/PS2_DAT0: J1007.1, R1014.2, U1001.27 (PB4)
/Slots and Peripherals/BMC/PS2_DAT1: J1007.7, R1016.2, U1001.28 (PB5)
/Slots and Peripherals/BMC/SPK_N: J1006.4, Q1003.3 (C)
/Slots and Peripherals/BMC/SPK_P: J1006.1, R1012.1
/Slots and Peripherals/BMC/SWCLK: J1001.4, U1001.24 (PA14)
/Slots and Peripherals/BMC/SWDIO: J1001.3, U1001.23 (PA13)
/Slots and Peripherals/BMC/~BMC_RST: J1001.2, U1001.4 (NRST)
/Slots and Peripherals/BMC/~BUTTON_PWR: J1002.1, SW1001.2, U1001.2 (PF0)
/Slots and Peripherals/BMC/~BUTTON_RST: J1003.1, SW1002.2, U1001.3 (PF1)
/Slots and Peripherals/BMC_SCL: JP403.1 (A), U402.11 (DDC_IN2), U1001.29 (PB6)
/Slots and Peripherals/BMC_SDA: JP404.1 (A), U402.10 (DDC_IN1), U1001.30 (PB7)
/Slots and Peripherals/FTDI_BRN: J901.2, U1001.22 (PA12)
/Slots and Peripherals/FTDI_GRN: J901.6, U1001.21 (PA11)
/Slots and Peripherals/FTDI_ORA: J901.4, U1001.20 (PA10)
/Slots and Peripherals/FTDI_YEL: J901.5, U1001.19 (PA9)
/Slots and Peripherals/PICO_SCL: J902.10 (I2C_SCL), J903.10 (I2C_SCL), J904.10 (I2C_SCL), J905.10 (I2C_SCL), J906.3, R202.1, U201.20 (GPIO15), U801.24 (SCLK), U1201.6 (SCL)
/Slots and Peripherals/PICO_SDA: J902.9 (I2C_SDA), J903.9 (I2C_SDA), J904.9 (I2C_SDA), J905.9 (I2C_SDA), J906.2, R201.1, U201.19 (GPIO14), U801.23 (SDIN), U1201.5 (SDA)
/Slots and Peripherals/SD Card/~WRITE_PROTECT: J1101.11 (WRITE_PROTECT), R1102.2
/Slots and Peripherals/SPI_CIPO: C303.1, C901.1, C902.1, C903.1, C904.1, C905.1, C906.1, J906.7, R301.2, R901.2, R902.2, R903.2, R904.2, R905.2, R906.2, U201.21 (GPIO16)
/Slots and Peripherals/SPI_CIPO_S0: R902.1, U1001.12 (PA6)
/Slots and Peripherals/SPI_CIPO_S1: J1101.7 (DAT0), R901.1
/Slots and Peripherals/SPI_CIPO_S2: J902.3 (SPI_CIPO), R903.1
/Slots and Peripherals/SPI_CIPO_S3: J903.3 (SPI_CIPO), R904.1
/Slots and Peripherals/SPI_CIPO_S4: J904.3 (SPI_CIPO), R905.1
/Slots and Peripherals/SPI_CIPO_S5: J905.3 (SPI_CIPO), R906.1
/Slots and Peripherals/SPI_CLK: C201.1, J902.5 (SPI_CLK), J903.5 (SPI_CLK), J904.5 (SPI_CLK), J905.5 (SPI_CLK), J906.5, J1101.5 (CLK), R203.2, U301.12 (SCK), U1001.11 (PA5)
/Slots and Peripherals/SPI_COPI: C202.1, J902.1 (SPI_COPI), J903.1 (SPI_COPI), J904.1 (SPI_COPI), J905.1 (SPI_COPI), J906.6, J1101.2 (CMD), R204.2, U301.13 (SI), U1001.13 (PA7)
/Slots and Peripherals/~RESET: J902.14 (~RESET), J903.14 (~RESET), J904.14 (~RESET), J905.14 (~RESET), J906.4, R1003.1, U201.30 (RUN), U301.18 (~RESET), U1001.8 (PA2)
/VGA_HSYNC: JP401.1 (A), U201.1 (GPIO0), U402.15 (SYNC_IN2)
/VGA_VSYNC: JP402.1 (A), U201.2 (GPIO1), U402.13 (SYNC_IN1)
/Video/BLUE_ANA: R708.1, R710.1, U401.3 (CH3_IN)
/Video/GREEN_ANA: R608.1, R610.1, U401.2 (CH2_IN)
/Video/RED_ANA: R508.1, R510.1, U401.1 (CH1_IN)
/Video/VGA_BLU: J401.3, R403.1, U402.3 (VIDEO1)
/Video/VGA_DDC_SCL: J401.15, JP403.2 (B), R406.2, U402.12 (DDC_OUT2)
/Video/VGA_DDC_SDA: J401.12, JP404.2 (B), R405.2, U402.9 (DDC_OUT1)
/Video/VGA_GRN: J401.2, R402.1, U402.4 (VIDEO2)
/Video/VGA_HSYNC_BUF: J401.13, JP401.2 (B), U402.16 (SYNC_OUT2)
/Video/VGA_RED: J401.1, R401.1, U402.5 (VIDEO3)
/Video/VGA_VSYNC_BUF: J401.14, JP402.2 (B), U402.14 (SYNC_OUT1)
GND: BT1201.2 (-), C201.2, C202.2, C301.2, C302.2, C303.2, C401.2, C402.1, C403.1, C404.1, C405.1, C801.2, C802.2, C803.2, C806.2, C807.2, C812.1, C813.1, C814.2, C815.2, C816.1, C817.2, C819.1, C901.2, C902.2, C903.2, C904.2, C905.2, C906.2, C1001.1, C1002.1, C1003.2, C1004.1, C1101.1, C1201.1, C1202.2, C1203.2, C1301.2, C1302.2, C1303.2, C1304.2, C1305.2, C1306.1, C1307.1, D1302.2 (A), J401.5, J401.6, J401.7, J401.8, J401.10, J801.2, J801.3, J802.2, J802.4, J803.2, J803.3, J901.1, J902.2 (GND), J902.4 (GND), J902.6 (GND), J902.19 (GND), J902.20 (GND), J903.2 (GND), J903.4 (GND), J903.6 (GND), J903.19 (GND), J903.20 (GND), J904.2 (GND), J904.4 (GND), J904.6 (GND), J904.19 (GND), J904.20 (GND), J905.2 (GND), J905.4 (GND), J905.6 (GND), J905.19 (GND), J905.20 (GND), J906.1, J907.1, J908.1, J1001.1, J1002.2, J1003.2, J1007.3, J1007.9, J1101.3 (VSS), J1101.6 (VSS), J1101.12 (SHELL1), J1101.13 (SHELL2), J1301.2, J1302.1, J1302.2, J1303.2, J1303.3, NT901.2, NT903.2, NT907.2, NT908.2, NT909.2, NT910.2, Q1001.2 (S), Q1002.2 (S), Q1003.2 (E), Q1303.2 (E), R307.2, R404.1, R509.2, R510.2, R609.2, R610.2, R709.2, R710.2, R801.2, R802.1, R803.2, R804.1, R805.1, R806.1, R809.2, R810.1, R1002.2, R1003.2, R1004.2, R1007.2, R1018.2, R1019.2, R1301.2, R1305.2, SW1001.1, SW1002.1, TP101.1, TP102.1, TP103.1, TP104.1, TP105.1, U201.3 (GND), U201.8 (GND), U201.13 (GND), U201.18 (GND), U201.23 (GND), U201.28 (GND), U201.33 (AGND), U201.38 (GND), U301.10 (VSS), U301.15 (A0), U301.16 (A1), U301.17 (A2), U302.8 (GND), U303.3 (GND), U401.5 (GND), U402.6 (GND), U801.11 (HPGND), U801.15 (AGND), U801.28 (DGND), U802.1 (Sleeve), U1001.16 (VSS), U1001.32 (VSS), U1201.4 (GND), U1301.3 (GND), U1302.1 (GND), U1303.1 (GND), Y801.2, Y801.4
unnamed: C810.1, C813.2, R807.2, R810.2
unnamed: C811.1, C812.2, R808.2, R809.1
unnamed: C818.2, R812.2
unnamed: D301.2 (A), R308.2
unnamed: D302.2 (A), R309.2
unnamed: D303.2 (A), R310.2
unnamed: D304.2 (A), R311.2
unnamed: D1001.1 (K), R1018.1
unnamed: D1002.1 (K), R1019.1
unnamed: D1301.2 (A), Q1301.1 (G), R1301.1
unnamed: C1301.1, D1301.1 (K), L1301.1, Q1301.2 (S), TP1301.1
unnamed: J401.0, R404.2
unnamed: J902.11 (EEPROM_ADDR0), NT901.1
unnamed: J902.12 (EEPROM_ADDR1), NT905.1
unnamed: J902.13 (EEPROM_ADDR2), NT909.1
unnamed: J903.11 (EEPROM_ADDR0), NT902.1
unnamed: J903.12 (EEPROM_ADDR1), NT906.1
unnamed: J903.13 (EEPROM_ADDR2), NT910.1
unnamed: J904.11 (EEPROM_ADDR0), NT903.1
unnamed: J904.12 (EEPROM_ADDR1), NT907.1
unnamed: J904.13 (EEPROM_ADDR2), NT911.1
unnamed: J905.11 (EEPROM_ADDR0), NT904.1
unnamed: J905.12 (EEPROM_ADDR1), NT908.1
unnamed: J905.13 (EEPROM_ADDR2), NT912.1
unnamed: J1004.1, R1008.2, R1009.2
unnamed: J1004.2, Q1001.3 (D)
unnamed: J1005.1, R1010.2, R1011.2
unnamed: J1005.2, Q1002.3 (D)
unnamed: F1301.2, J1301.1, J1302.3, J1302.4
unnamed: JP201.1 (A), Q201.1 (G), U201.40 (VBUS)
unnamed: JP1001.2 (B), R1004.1, U1001.31 (BOOT0)
unnamed: C1201.2, JP1201.1 (A), JP1202.1 (A), U1201.8 (VCC)
unnamed: Q201.2 (S), U201.39 (VSYS)
unnamed: Q1003.1 (B), R1017.2
unnamed: F1301.1, Q1301.3 (D)
unnamed: Q1302.1 (B), R1302.1
unnamed: Q1302.3 (C), R1304.2, R1305.1
unnamed: Q1303.1 (B), R1303.1
unnamed: Q1303.3 (C), R1302.2
unnamed: R501.2, R505.2, R509.1
unnamed: R502.2, R505.1, R506.2
unnamed: R503.2, R506.1, R507.2
unnamed: R504.2, R507.1, R508.2
unnamed: R601.2, R605.2, R609.1
unnamed: R602.2, R605.1, R606.2
unnamed: R603.2, R606.1, R607.2
unnamed: R604.2, R607.1, R608.2
unnamed: R701.2, R705.2, R709.1
unnamed: R702.2, R705.1, R706.2
unnamed: R703.2, R706.1, R707.2
unnamed: R704.2, R707.1, R708.2
unnamed: R1005.2, R1006.1
unnamed: R203.1, U201.24 (GPIO18)
unnamed: R204.1, U201.25 (GPIO19)
unnamed: R301.1, U301.14 (SO)
unnamed: R401.2, U401.8 (CH1_OUT)
unnamed: R402.2, U401.7 (CH2_OUT)
unnamed: R403.2, U401.6 (CH3_OUT)
unnamed: C402.2, U402.8 (BYP)
unnamed: R805.2, U801.22 (MODE)
unnamed: C817.1, U801.25 (XTI/MCK), Y801.1
unnamed: C816.2, U801.26 (XTO), Y801.3
unnamed: R806.2, U801.21 (~CS)
unnamed: C1202.1, U1201.1 (X1), Y1201.1
unnamed: C1203.1, U1201.2 (X2), Y1201.2
VDC: C1302.1, C1306.2, L1301.2, Q1302.2 (E), U1301.2 (Vin), U1303.2 (VIN)

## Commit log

2025-04-22 Add microBTX conversion specifications and documentation
2025-04-22 Add microBTX conversion implementation and documentation
2025-04-22 Add converted microBTX PCB file
2025-04-22 Implement microBTX conversion for Neotron-Pico
    - Convert ATX-compatible board to microBTX form factor
    - Mirror board outline to match microBTX specifications (264mm x 267mm)
    - Reposition components according to category classification
    - Maintain signal integrity and trace routing
    - Add comprehensive documentation for the conversion process
    - Include verification steps for expansion slots, signal integrity, and geometric soundness
2025-04-22 Add PR description
2025-04-22 Remove PR description file from repository
2025-04-22 Add microBTX PCB file and conversion scripts
2025-04-22 Fix date in microBTX PCB file
2025-04-22 Add microBTX conversion documentation
2025-04-22 Add DRC verification documentation
2025-04-22 - Enhance conversion report with comprehensive details
2025-04-22 - Add detailed component lists for each category
2025-04-22 - Add references to KiCad documentation and forum discussions
2025-04-22 - Update conversion scripts with DRC violation handling
2025-04-22 - Generate component_analysis.json with complete component data
2025-04-22 - Include DRC report with violation counts
2025-04-22 - Ensure proper handling of all component types
2025-04-22 - Clarify that mounting holes need to be recreated for BTX compatibility
2025-04-22 - Ensure compatibility with BTX cases
2025-04-22 - Ensure all verification aspects from the playbook are covered
2025-04-22 Complete remaining BTX conversion steps: - Add thermal design verification documentation - Add schematic parity verification documentation - Document remaining DRC violations - Complete all verificat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
2025-04-22 Update schematic parity verification documentation with actual test results
2025-04-22 Update component classification statistics in conversion report
2025-04-22 Add implementation verification document and image placeholder
2025-04-22 Complete microBTX conversion with proper board dimensions and mounting holes
2025-04-23 Add SRM mounting hole verification and documentation
2025-04-23 Add SRM mounting hole position verification and region analysis
2025-04-23 Add microBTX compliance verification document
2025-04-23 Add comprehensive SRM verification summary document
2025-04-23 Add layer dimension analysis and verification scripts
2025-04-23 Add component repositioning, trace rerouting, and layer footprint verification
2025-04-23 Add comprehensive verification scripts and implementation summary
2025-04-24 Add PCB layout visualization and conversion image documentation
2025-04-25 Complete BTX conversion with SRM mounting holes and verification
2025-04-25 Fix component classification count in verification summary

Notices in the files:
README.md:
Licence:
These documents, schematics and PCB designs are Copyright (c) The Neotron Developers, 2022.
This work is licensed under a [Creative Commons Attribution-ShareAlike 4.0 International License](http://creativecommons.org/licenses/by-sa/4.0/).
That means you are free to:
share - copy and redistribute the material in any medium or format
adapt — remix, transform, and build upon the material for any purpose, even commercially
Please note that the models provided in the [Ki
Kicad/neotron-pico-btx.kicad_pcb:
Copyright (c) Jonathan 'theJPster' Pallant 2022
Licensed as CC-BY-SA
